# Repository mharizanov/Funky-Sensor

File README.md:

Funky-Sensor
============

Funky Sensor stuff

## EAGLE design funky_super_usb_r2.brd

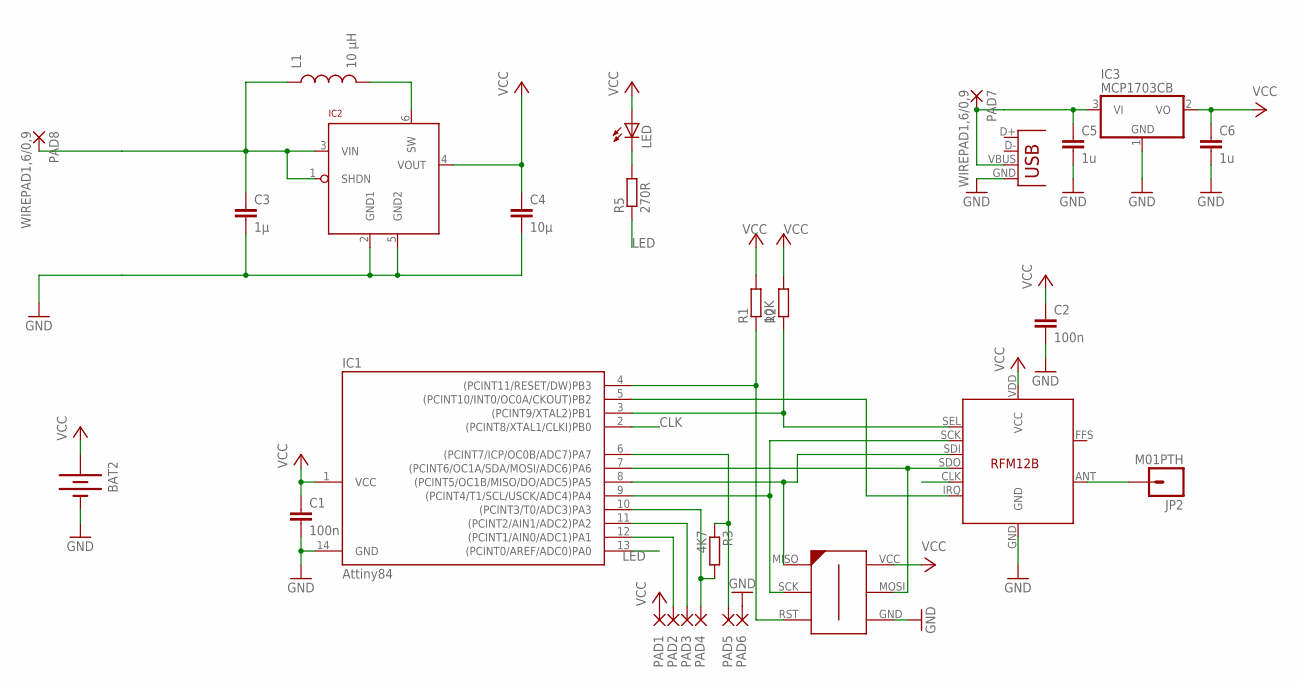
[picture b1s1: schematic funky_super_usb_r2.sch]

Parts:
BAT2: BATTERY20PTH; BATTCOM_20MM_PTH
C1, C2: 100n; C0603K
C3: 1µ; 0603-CAP
C4: 10µ; 0805
C5, C6: 1u; C0603K
IC1: Attiny84; SOIC14
IC2: LTC3525; SC70
IC3: MCP1703CB; SOT23
JP2: M01PTH; 1X01
L1: 10 µH; 1210
LED: LED0603; LED-0603
PAD1, PAD2, PAD3, PAD4, PAD5, PAD6: SMD2; SMD1,27-2,54
PAD7, PAD8: WIREPAD1,6/0,9; 1,6/0,9
R1: 10K; R0603
R2: R-EU_R0603; R0603
R3: 4K7; R0603
R5: 270R; R0603
RFM12B: RFM12B
U$2: AVR-ISP-6-EDGE; 6PAD_ISP
X1: USB-MICROB

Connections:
CLK: IC1.2 ((PCINT8/XTAL1/CLKI)PB0), RFM12B.CLK
GND: BAT2.2 (-), C1.2, C2.2, C3.2, C4.2, C5.2, C6.2, IC1.14 (GND), IC2.2 (GND1), IC2.5 (GND2), IC3.1 (GND), PAD6.1, RFM12B.GND, U$2.GND, X1.GND
LED: IC1.13 ((PCINT0/AREF/ADC0)PA0), R5.1
unnamed: IC1.4 ((PCINT11/RESET/DW)PB3), R1.1, U$2.RST
unnamed: IC1.3 ((PCINT9/XTAL2)PB1), R2.1, RFM12B.SEL
unnamed: JP2.1, RFM12B.ANT
unnamed: IC1.9 ((PCINT4/T1/SCL/USCK/ADC4)PA4), RFM12B.SCK, U$2.SCK
unnamed: IC1.8 ((PCINT5/OC1B/MISO/DO/ADC5)PA5), RFM12B.SDI, U$2.MISO
unnamed: IC1.7 ((PCINT6/OC1A/SDA/MOSI/ADC6)PA6), RFM12B.SDO, U$2.MOSI
unnamed: IC1.5 ((PCINT10/INT0/OC0A/CKOUT)PB2), RFM12B.IRQ
unnamed: IC1.6 ((PCINT7/ICP/OC0B/ADC7)PA7), PAD5.1, R3.1
unnamed: IC1.10 ((PCINT3/T0/ADC3)PA3), PAD4.1, R3.2
unnamed: IC1.11 ((PCINT2/AIN1/ADC2)PA2), PAD3.1
unnamed: IC1.12 ((PCINT1/AIN0/ADC1)PA1), PAD2.1
unnamed: LED.C, R5.2
unnamed: IC2.6 (SW), L1.2
unnamed: C5.1, IC3.3 (VI), PAD7.1, X1.VBUS
VCC: BAT2.1 (+), C1.1, C2.1, C4.1, C6.1, IC1.1 (VCC), IC2.4 (VOUT), IC3.2 (VO), LED.A, PAD1.1, R1.2, R2.2, RFM12B.VDD (VCC), U$2.VCC
VIN: C3.1, IC2.1 (SHDN), IC2.3 (VIN), L1.1, PAD8.1

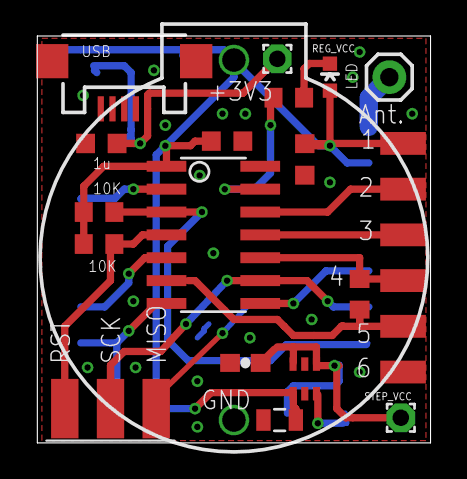
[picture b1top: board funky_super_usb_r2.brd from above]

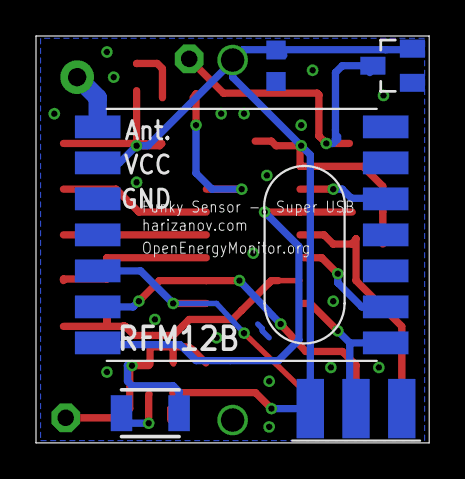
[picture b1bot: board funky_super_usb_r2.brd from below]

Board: 2 copper layers, 21.8 x 22.6 mm, 28 parts (4 on the bottom side), 19 nets.

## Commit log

2012-09-24 ignore temp eagle files
2012-09-24 first
2012-09-24 added 3d model and renderings
2012-09-28 edited silk and reduced vias
2012-10-12 minor silk revisions
2012-10-31 examples added
2012-11-01 minor fixes
2012-11-21 minor change from 1Mhz to 8Mhz
2012-11-27 Pin 10 in new revision
2012-12-17 added LED candle
2013-01-05 Increased delay before reading the DHT22
2013-01-10 Added a delay to make led blink visible
2013-01-21 improvements :)
2013-02-22 ACK fine-tuning
2013-02-22 Addiny my emonGLCD code with Funky+DHT22 readout
2013-05-27 LTC3108 experiment
2013-07-07 more power efficient code
2014-01-15 DVR sensor code
2015-01-29 Examples update

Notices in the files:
parts and their libraries:
SparkFun: Licensing: CC v3.0 Share-Alike You are welcome to use this library for commercial purposes.
